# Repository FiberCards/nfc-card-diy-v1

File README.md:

# FiberCards NFC Business Card DIY Kit

A DIY kit for building your own battery-free NFC business card. Assemble the board, then tap it with an NFC-enabled phone to share a link and light up the LEDs.
The copper spiral on the board acts as an inductor and NFC antenna. The phone's changing magnetic field induces a voltage in the coil, and the NFC chip harvests this energy to power the microcontroller and LEDs. To reprogram the NFC chip, you can do so using your phone, through an app such as [NFC Tools](https://nfc.software/en).

The hardware design is in [`cad/`](cad/), and the firmware is in [`firmware/`](firmware/).

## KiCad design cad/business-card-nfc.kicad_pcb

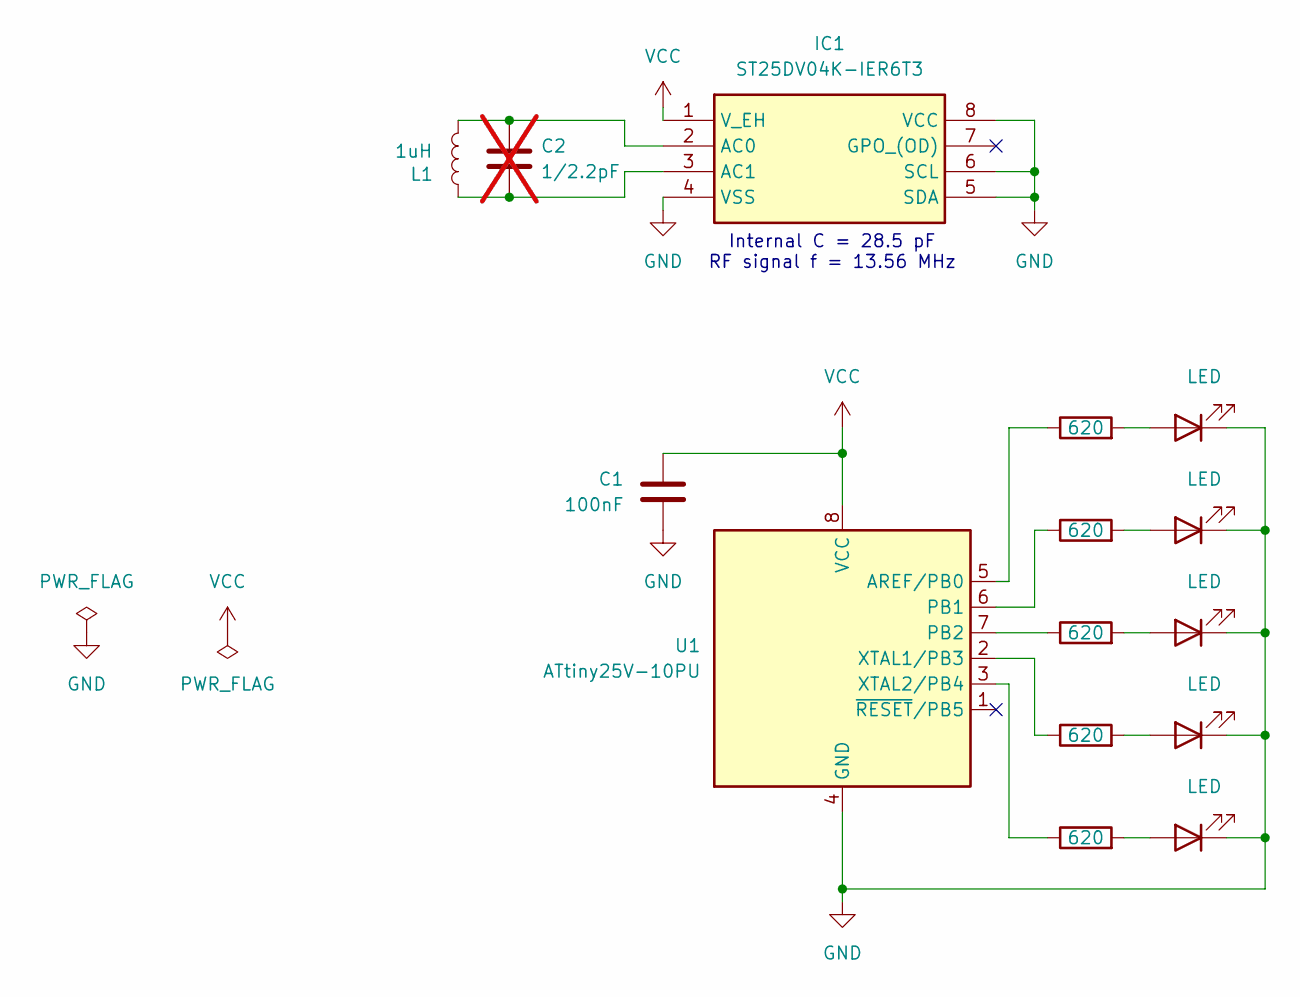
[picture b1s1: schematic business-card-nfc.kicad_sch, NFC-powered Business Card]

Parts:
C1: 100nF; C_Disc_D3.0mm_W1.6mm_P2.50mm
C2: 1/2.2pF; C_0603_1608Metric; Manufacturer_Part_Number GCM1885C2A111JA16D; not fitted
D1, D2, D3, D4, D5: LED; LED_D5.0mm
IC1: ST25DV04K-IER6T3; SOP65P640X120-8N; Mouser Part Number 511-ST25DV04K-IER6T3
L1: 1uH; NFC_Tag_Antenna_40.0mm_4.641uH
R1, R2, R3, R4, R5: 620; R_Axial_DIN0207_L6.3mm_D2.5mm_P7.62mm_Horizontal
U1: ATtiny25V-10PU; DIP-8_W7.62mm_Socket_LongPads

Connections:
GND: C1.2, D1.1 (K), D2.1 (K), D3.1 (K), D4.1 (K), D5.1 (K), IC1.4 (VSS), IC1.5 (SDA), IC1.6 (SCL), IC1.8 (VCC), U1.4 (GND)
unnamed: D1.2 (A), R1.2
unnamed: D2.2 (A), R2.2
unnamed: D3.2 (A), R3.2
unnamed: D4.2 (A), R4.2
unnamed: D5.2 (A), R5.2
unnamed: C2.1, IC1.2 (AC0), L1.1
unnamed: C2.2, IC1.3 (AC1), L1.2
unnamed: R1.1, U1.5 (AREF/PB0)
unnamed: R2.1, U1.6 (PB1)
unnamed: R3.1, U1.7 (PB2)
unnamed: R4.1, U1.2 (XTAL1/PB3)
unnamed: R5.1, U1.3 (XTAL2/PB4)
VCC: C1.1, IC1.1 (V_EH), U1.8 (VCC)

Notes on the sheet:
Internal C = 28.5 pF RF signal f = 13.56 MHz

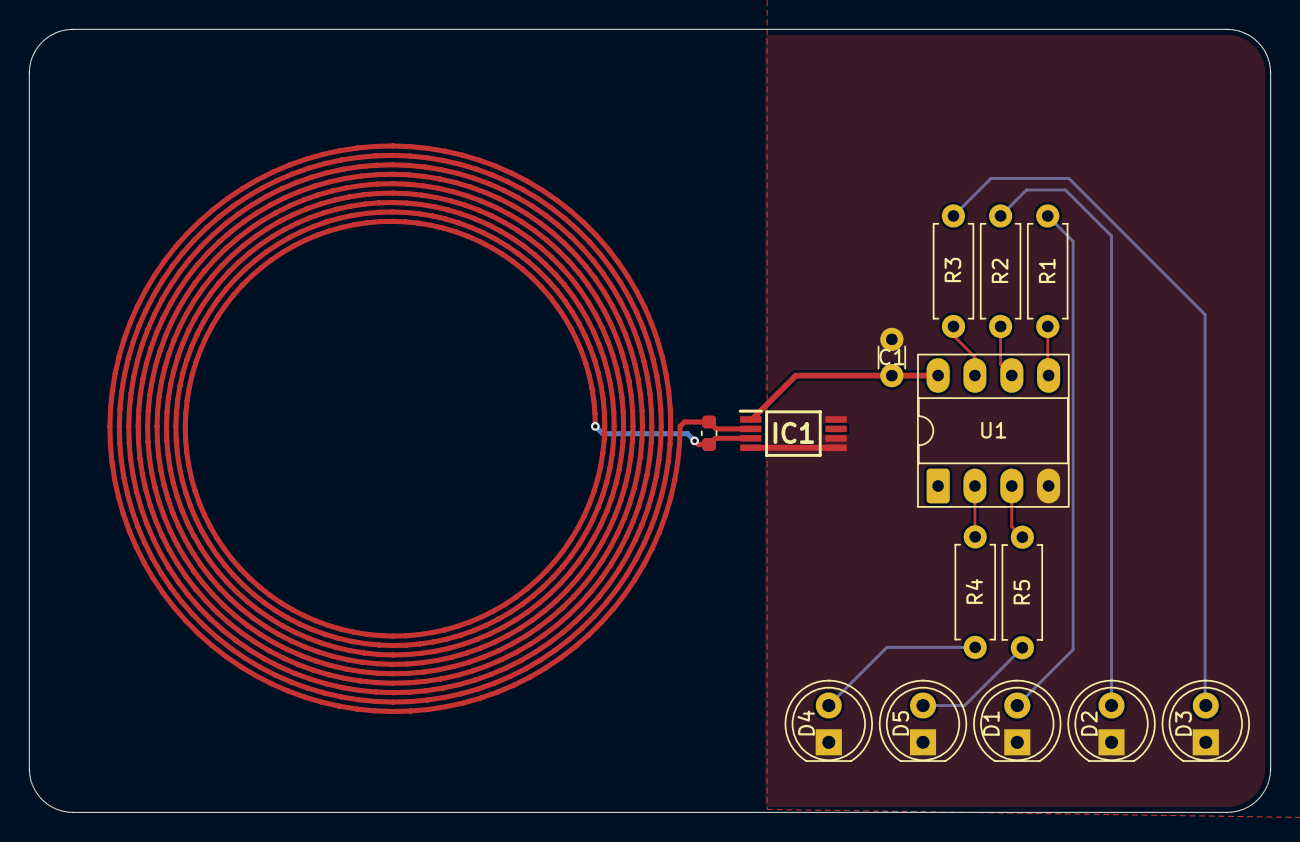
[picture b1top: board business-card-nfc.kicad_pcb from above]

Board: 2 copper layers, 85.6 x 54.0 mm, 15 parts (0 on the bottom side), 14 nets.
